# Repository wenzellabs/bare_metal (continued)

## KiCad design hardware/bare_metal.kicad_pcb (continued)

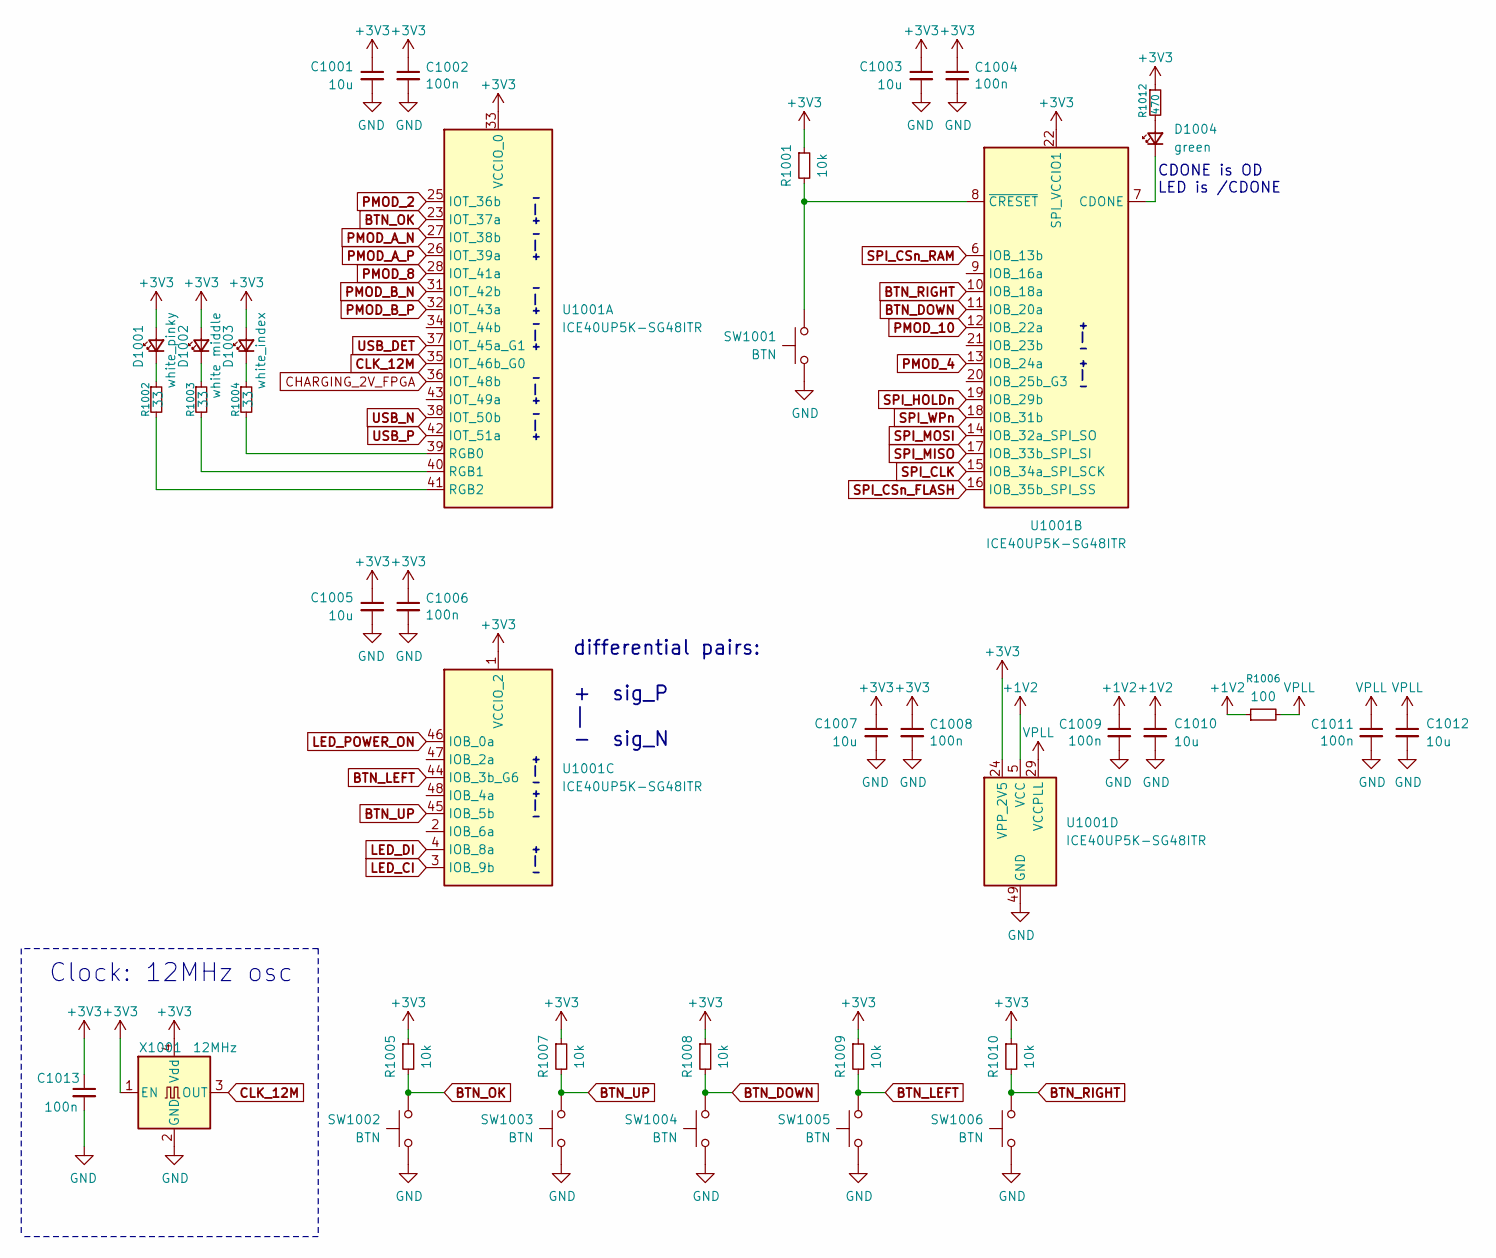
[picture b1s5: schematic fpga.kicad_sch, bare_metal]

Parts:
C1001, C1003, C1005, C1007, C1010, C1012: 10u; C_0603_1608Metric
C1002, C1004, C1006, C1008, C1009, C1011, C1013: 100n; C_0402_1005Metric
D1001: white_pinky; LED_0805_2012Metric
D1002: white middle; LED_0805_2012Metric
D1003: white_index; LED_0805_2012Metric
D1004: green; LED_0805_2012Metric
R1001, R1005, R1007, R1008, R1009, R1010: 10k; R_0402_1005Metric
R1002, R1003, R1004: 33; R_0402_1005Metric
R1006: 100; R_0402_1005Metric
R1012: 470; R_0402_1005Metric
SW1001, SW1002, SW1003, SW1004, SW1005, SW1006: BTN; SW_Push_1P1T_XKB_TS-1187A
U1001: ICE40UP5K-SG48ITR; QFN-48-1EP_7x7mm_P0.5mm_EP5.6x5.6mm
X1001: 12MHz; Crystal_SMD_3225-4Pin_3.2x2.5mm

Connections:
+1V2: C1009.1, C1010.1, R1006.1, U1001.5 (VCC), U1001.30 (VCC); also elsewhere on the board
+3V3: C1001.1, C1002.1, C1003.1, C1004.1, C1005.1, C1006.1, C1007.1, C1008.1, C1013.1, D1001.2 (A), D1002.2 (A), D1003.2 (A), R1001.1, R1005.1, R1007.1, R1008.1, R1009.1, R1010.1, R1012.1, U1001.1 (VCCIO_2), U1001.22 (SPI_VCCIO1), U1001.24 (VPP_2V5), U1001.33 (VCCIO_0), X1001.1 (EN), X1001.4 (Vdd); also elsewhere on the board
BTN_DOWN: R1008.2, SW1004.1, U1001.11 (IOB_20a)
BTN_LEFT: R1009.2, SW1005.1, U1001.44 (IOB_3b_G6)
BTN_OK: R1005.2, SW1002.1, U1001.23 (IOT_37a)
BTN_RIGHT: R1010.2, SW1006.1, U1001.10 (IOB_18a)
BTN_UP: R1007.2, SW1003.1, U1001.45 (IOB_5b)
CHARGING_2V_FPGA: U1001.36 (IOT_48b); also elsewhere on the board
CLK_12M: U1001.35 (IOT_46b_G0), X1001.3 (OUT)
GND: C1001.2, C1002.2, C1003.2, C1004.2, C1005.2, C1006.2, C1007.2, C1008.2, C1009.2, C1010.2, C1011.2, C1012.2, C1013.2, SW1001.2, SW1002.2, SW1003.2, SW1004.2, SW1005.2, SW1006.2, U1001.49 (GND), X1001.2 (GND); also elsewhere on the board
LED_CI: U1001.3 (IOB_9b); also elsewhere on the board
LED_DI: U1001.4 (IOB_8a); also elsewhere on the board
LED_POWER_ON: U1001.46 (IOB_0a); also elsewhere on the board
unnamed: D1001.1 (K), R1002.1
unnamed: D1002.1 (K), R1003.1
unnamed: D1003.1 (K), R1004.1
unnamed: D1004.2 (A), R1012.2
unnamed: D1004.1 (K), U1001.7 (CDONE)
unnamed: R1004.2, U1001.39 (RGB0)
unnamed: R1003.2, U1001.40 (RGB1)
unnamed: R1002.2, U1001.41 (RGB2)
unnamed: R1001.2, SW1001.1, U1001.8 (~CRESET)
PMOD_2: U1001.25 (IOT_36b); also elsewhere on the board
PMOD_4: U1001.13 (IOB_24a); also elsewhere on the board
PMOD_8: U1001.28 (IOT_41a); also elsewhere on the board
PMOD_10: U1001.12 (IOB_22a); also elsewhere on the board
PMOD_A_N: U1001.27 (IOT_38b); also elsewhere on the board
PMOD_A_P: U1001.26 (IOT_39a); also elsewhere on the board
PMOD_B_N: U1001.31 (IOT_42b); also elsewhere on the board
PMOD_B_P: U1001.32 (IOT_43a); also elsewhere on the board
SPI_CLK: U1001.15 (IOB_34a_SPI_SCK); also elsewhere on the board
SPI_CSn_FLASH: U1001.16 (IOB_35b_SPI_SS); also elsewhere on the board
SPI_CSn_RAM: U1001.6 (IOB_13b); also elsewhere on the board
SPI_HOLDn: U1001.19 (IOB_29b); also elsewhere on the board
SPI_MISO: U1001.17 (IOB_33b_SPI_SI); also elsewhere on the board
SPI_MOSI: U1001.14 (IOB_32a_SPI_SO); also elsewhere on the board
SPI_WPn: U1001.18 (IOB_31b); also elsewhere on the board
USB_DET: U1001.37 (IOT_45a_G1); also elsewhere on the board
USB_N: U1001.38 (IOT_50b); also elsewhere on the board
USB_P: U1001.42 (IOT_51a); also elsewhere on the board
VPLL: C1011.1, C1012.1, R1006.2, U1001.29 (VCCPLL)

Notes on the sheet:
+ | -
- | +
differential pairs: + sig_P | - sig_N
Clock: 12MHz osc
CDONE is OD LED is /CDONE

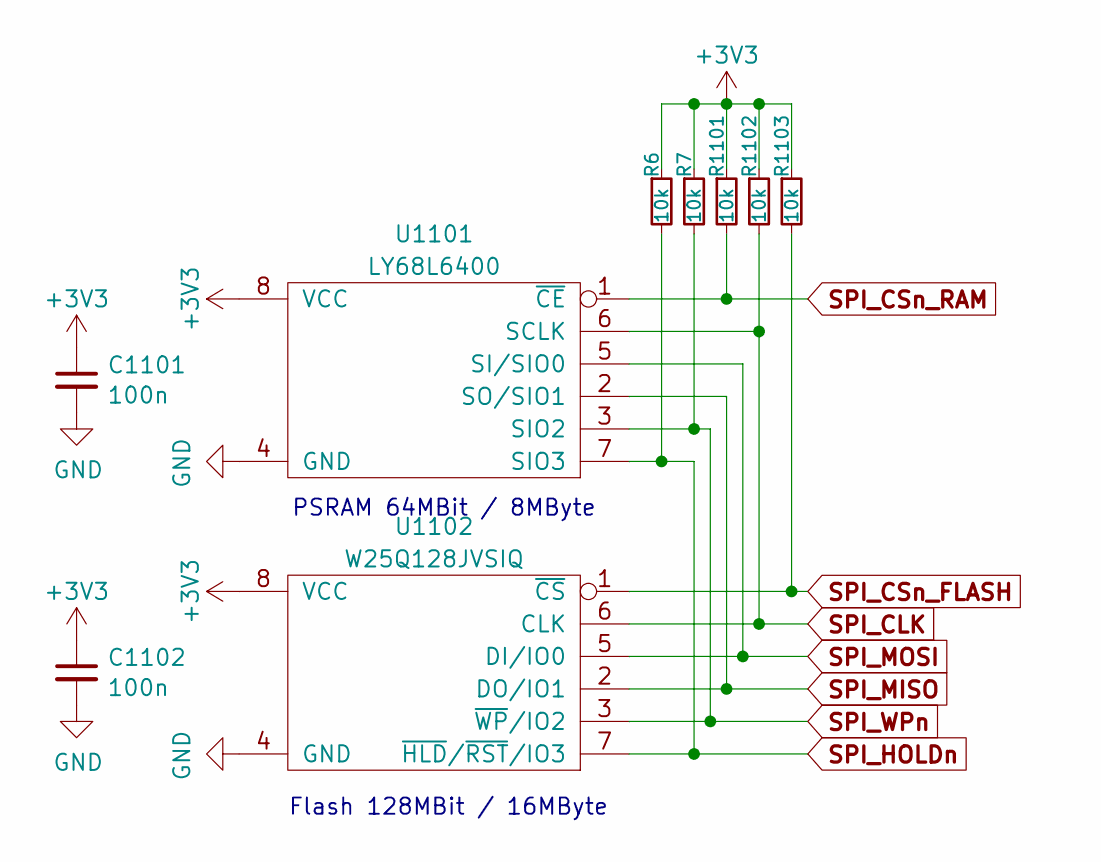
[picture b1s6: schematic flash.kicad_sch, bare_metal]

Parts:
C1101, C1102: 100n; C_0402_1005Metric
R6, R7, R1101, R1102, R1103: 10k; R_0402_1005Metric
U1101: LY68L6400; SOIC-8_3.9x4.9mm_P1.27mm
U1102: W25Q128JVSIQ; SOIC-8_5.3x5.3mm_P1.27mm

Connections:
+3V3: C1101.1, C1102.1, R6.1, R7.1, R1101.1, R1102.1, R1103.1, U1101.8 (VCC), U1102.8 (VCC); also elsewhere on the board
GND: C1101.2, C1102.2, U1101.4 (GND), U1102.4 (GND); also elsewhere on the board
SPI_CLK: R1102.2, U1101.6 (SCLK), U1102.6 (CLK); also elsewhere on the board
SPI_CSn_FLASH: R1103.2, U1102.1 (~CS); also elsewhere on the board
SPI_CSn_RAM: R1101.2, U1101.1 (~CE); also elsewhere on the board
SPI_HOLDn: R6.2, U1101.7 (SIO3), U1102.7 (~HLD/~RST/IO3); also elsewhere on the board
SPI_MISO: U1101.2 (SO/SIO1), U1102.2 (DO/IO1); also elsewhere on the board
SPI_MOSI: U1101.5 (SI/SIO0), U1102.5 (DI/IO0); also elsewhere on the board
SPI_WPn: R7.2, U1101.3 (SIO2), U1102.3 (~WP/IO2); also elsewhere on the board

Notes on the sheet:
PSRAM 64MBit / 8MByte
Flash 128MBit / 16MByte

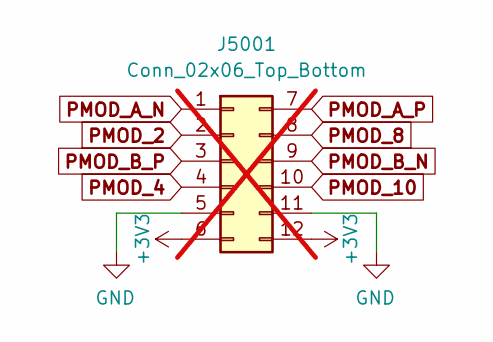
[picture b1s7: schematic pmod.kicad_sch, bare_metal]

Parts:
J5001: Conn_02x06_Top_Bottom; PMOD_PinSocket_2x06_P2.54mm_Horizontal; not fitted

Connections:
+3V3: J5001.6, J5001.12; also elsewhere on the board
GND: J5001.5, J5001.11; also elsewhere on the board
PMOD_2: J5001.2; also elsewhere on the board
PMOD_4: J5001.4; also elsewhere on the board
PMOD_8: J5001.8; also elsewhere on the board
PMOD_10: J5001.10; also elsewhere on the board
PMOD_A_N: J5001.1; also elsewhere on the board
PMOD_A_P: J5001.7; also elsewhere on the board
PMOD_B_N: J5001.9; also elsewhere on the board
PMOD_B_P: J5001.3; also elsewhere on the board

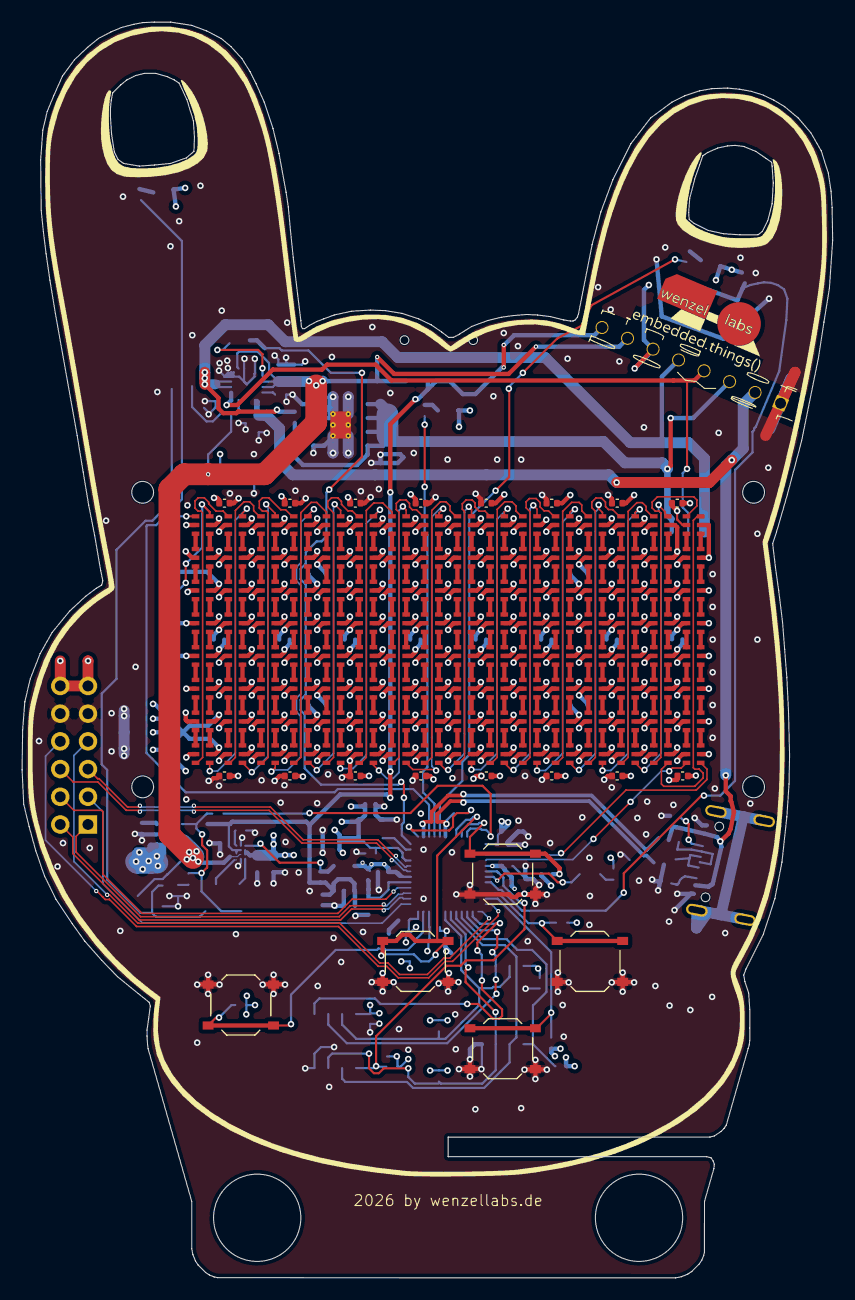
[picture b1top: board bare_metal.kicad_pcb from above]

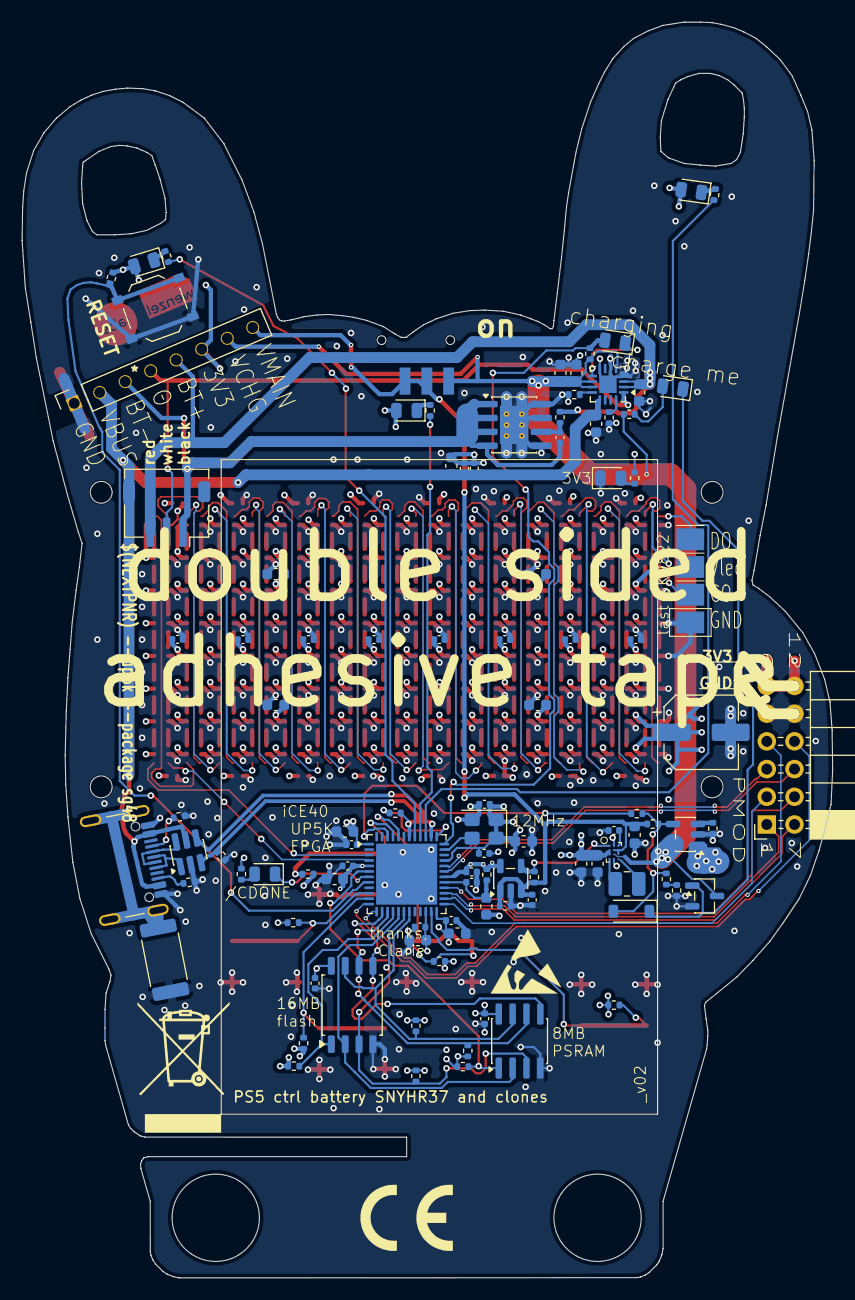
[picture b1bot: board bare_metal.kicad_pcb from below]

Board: 4 copper layers, 74.3 x 115.1 mm, 257 parts (103 on the bottom side), 323 nets.

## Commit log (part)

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2026-04-18 initial commit, just an early README
2026-04-19 hackerstacker, nick, image, pattern, rainbow work. on the wong display.
2026-04-19 multiple nick support. yes the fonts are still wong
2026-04-19 multiple images support
2026-04-19 brightness controlm through up and down buttons
2026-04-19 rot images to correct orientation
2026-04-19 limit brightness to 15, anything els is nuts, and gets warm, and the 2A HW limiter for LED power kicks in
2026-04-19 limit brightness to 9 even, LED area feels > 60°C still, need to measure
2026-04-19 more pattern and rainbow modes
2026-04-20 nick and font good enough for a commit, image now uses DSP multi not generated logic, d'oh
2026-04-20 actually add two free TTF fonts
2026-04-20 change some defaults
2026-04-20 clean up Makefile
2026-04-21 save around 360 logic cells in image.py
    reduced allowed image dimensiond from 64k x 64k to 1024 x 1024
    saves 360 cells, here's the sweep, 8 bit through 16 bit
    image_width and image_height CSV:
    bit_width and bit_height in image module, cells used by image module
    8,1524
    9,1600
2026-04-21 allow dimmer brightness by shifting down R, G and B values by up to 7
2026-04-21 allow long nicks (up to 256 chars)
2026-04-21 more fonts, more magic into flash-font
2026-04-21 fix hackerstacker winner screen
2026-04-23 rename a few
2026-04-23 allow flashing of foreign bins, and to all slots
    make flash SLOT=2 BIN=/some/alien.bin
    which can then be booted by pressing btn_left during reset/power up.
    make flash SLOT=3 BIN=/home/brew.bin
    which can then be booted by pressing btn_right during reset/power up.
2026-04-24 add an initial verilog julia set
2026-04-24 indentation
2026-04-24 some first dynamic zoom in and out again
2026-04-24 pan instead of jump to new random P
2026-04-24 adjust zoom speeds
2026-04-24 julia: 8 palettes with btn_ok
2026-05-05 some more doc in README.md
2026-05-05 add julia Makefile targets 'report timing stats help'
2026-05-05 hackerstacker_demo: transgender flag modes, approaching 100% LCs
2026-05-05 rm dup color logic, simplify stacker winning screen (no HSV conv)
2026-05-05 add make gui (nextpnr) and make svg
2026-05-06 julia: rm flash_controller.v
2026-05-12 add initial VGA PMOD demo
2026-05-13 more VGA modes
